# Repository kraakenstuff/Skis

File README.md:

# Skis

This is smd version of Bastl Skis v1. Main differences are:

* It has skis (two sliders) vs. no skis in Bastl version
* 6HP vs. 5HP, for obvious, OCD reasons
* Range switch vs. range backside jumper (although this switch works as a jumper - instead of going from freq0 to freq1, and then from freq1 to freq2 in the second position, it goes from freq0 to freq1, and then from freq0 to freq2)
* Version 2 of Bastl Skis has decay CV input, and this one doesn't have it
* Version 1 of Bastl Skis was THT and had two sandwiched boards, and this one is SMT in one board.

Status: tested and working.

CC-BY-SA
Václav Peloušek
bastl-instruments.com

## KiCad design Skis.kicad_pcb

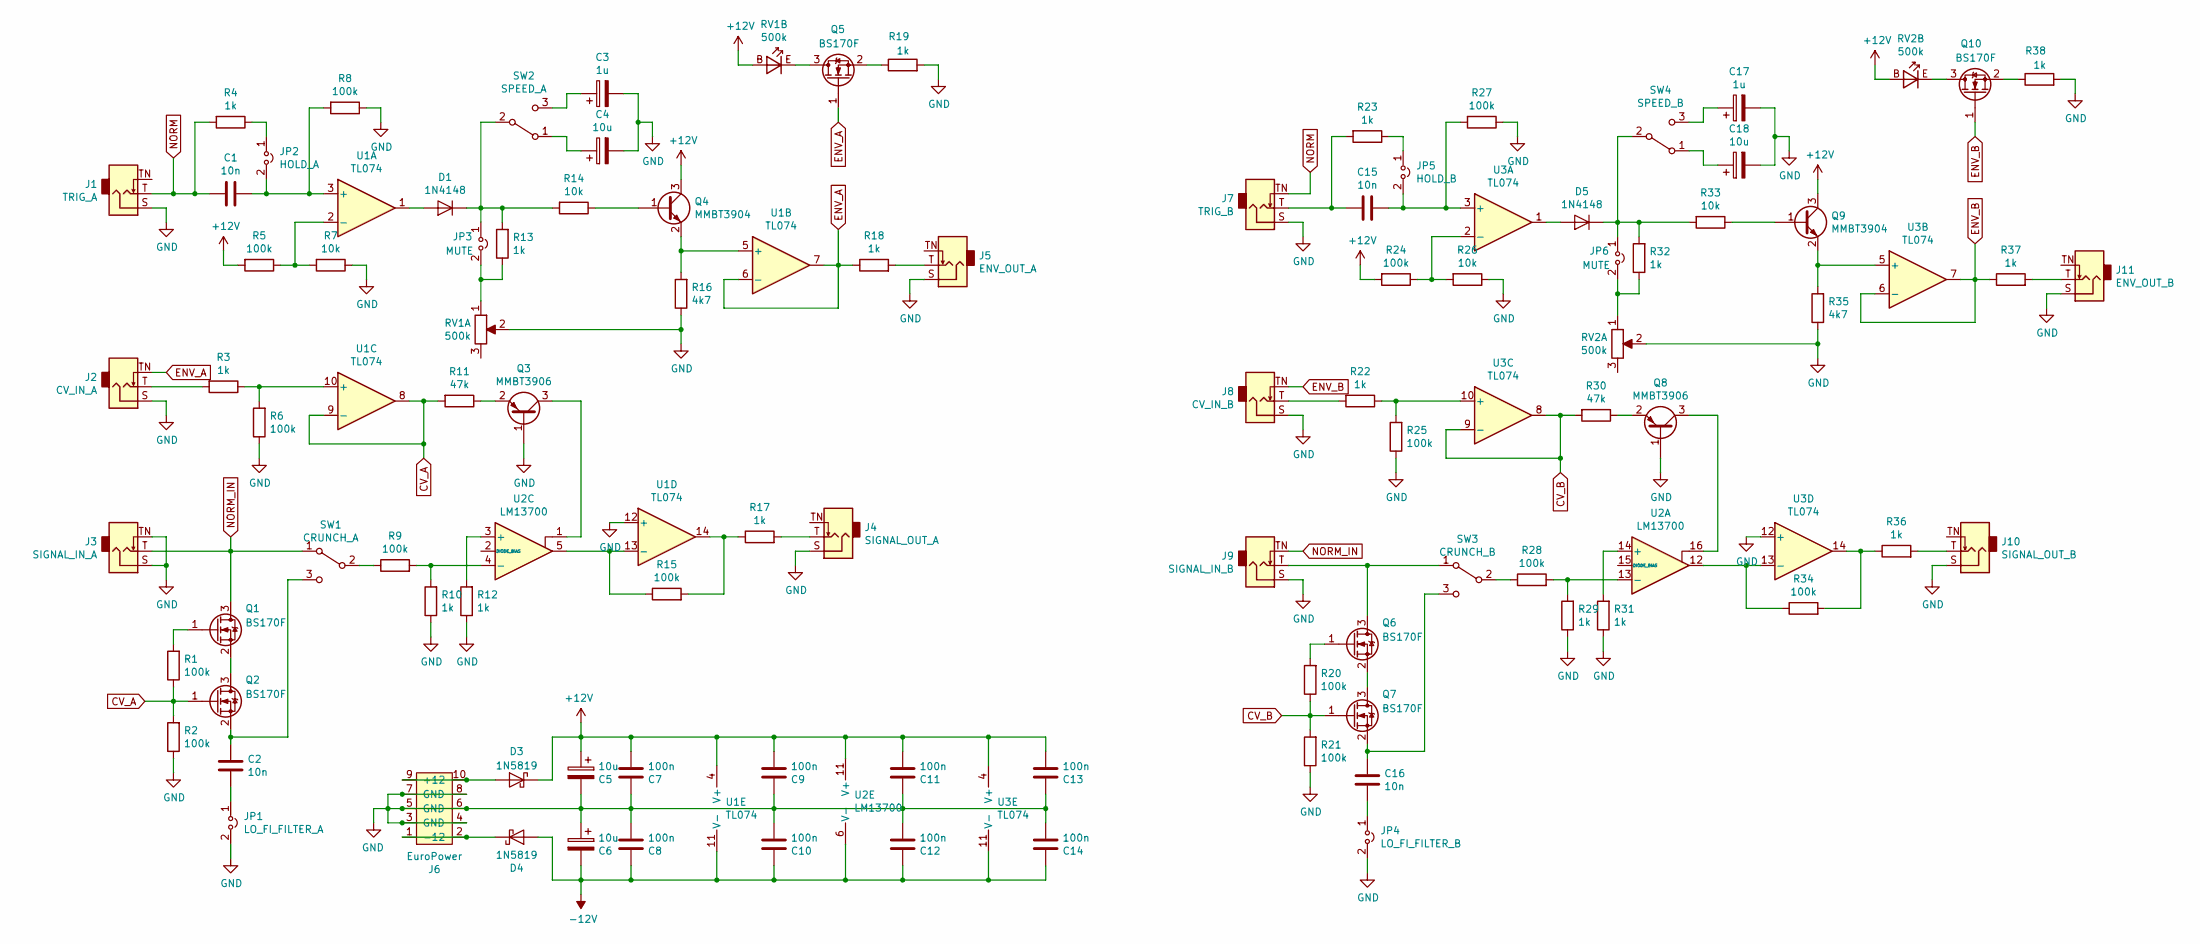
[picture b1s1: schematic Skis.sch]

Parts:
C1, C2, C15, C16: 10n; C_0603_1608Metric_Pad1.05x0.95mm_HandSolder
C3, C17: 1u; CP_Elec_4x5.8
C4, C5, C6, C18: 10u; CP_Elec_5x5.8
C7, C8, C9, C10, C11, C12, C13, C14: 100n; C_0603_1608Metric_Pad1.05x0.95mm_HandSolder
D1, D5: 1N4148; D_0603_1608Metric_Pad1.05x0.95mm_HandSolder
D3, D4: 1N5819; D_SOD-123
J1: TRIG_A; PJ301M-12-NoHole
J2: CV_IN_A; PJ301M-12-NoHole
J3: SIGNAL_IN_A; PJ301M-12-NoHole
J4: SIGNAL_OUT_A; PJ301M-12-NoHole
J5: ENV_OUT_A; PJ301M-12-NoHole
J6: EuroPower; EuroHeader10
J7: TRIG_B; PJ301M-12-NoHole
J8: CV_IN_B; PJ301M-12-NoHole
J9: SIGNAL_IN_B; PJ301M-12-NoHole
J10: SIGNAL_OUT_B; PJ301M-12-NoHole
J11: ENV_OUT_B; PJ301M-12-NoHole
JP1: LO_FI_FILTER_A; Header 1x2
JP2: HOLD_A; Header 1x2
JP3, JP6: MUTE; Header 1x2
JP4: LO_FI_FILTER_B; Header 1x2
JP5: HOLD_B; Header 1x2
Q1, Q2, Q5, Q6, Q7, Q10: BS170F; SOT-23
Q3, Q8: MMBT3906; SOT-23
Q4, Q9: MMBT3904; SOT-23
R1, R2, R5, R6, R8, R9, R15, R20, R21, R24, R25, R27, R28, R34: 100k; R_0603_1608Metric_Pad1.05x0.95mm_HandSolder
R3, R4, R10, R12, R13, R17, R18, R19, R22, R23, R29, R31, R32, R36, R37, R38: 1k; R_0603_1608Metric_Pad1.05x0.95mm_HandSolder
R7, R14, R26, R33: 10k; R_0603_1608Metric_Pad1.05x0.95mm_HandSolder
R11, R30: 47k; R_0603_1608Metric_Pad1.05x0.95mm_HandSolder
R16, R35: 4k7; R_0603_1608Metric_Pad1.05x0.95mm_HandSolder
RV1, RV2: 500k; PTL30
SW1: CRUNCH_A; SubSwitch_SPDT
SW2: SPEED_A; SubSwitch_SPDT
SW3: CRUNCH_B; SubSwitch_SPDT
SW4: SPEED_B; SubSwitch_SPDT
U1, U3: TL074; SSOP-14_5.3x6.2mm_P0.65mm
U2: LM13700; SOIC-16W_5.3x10.2mm_P1.27mm

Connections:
+12V: C5.1, C7.1, C9.1, C11.1, C13.1, D3.1 (K), Q4.3 (C), Q9.3 (C), R5.2, R24.2, RV1.B, RV2.B, U1.4 (V+), U2.11 (V+), U3.4 (V+)
-12V: C6.2, C8.2, C10.2, C12.2, C14.2, D4.2 (A), U1.11 (V-), U2.6 (V-), U3.11 (V-)
CV_A: Q2.1 (G), R1.1, R2.2, R11.2, U1.8, U1.9 (-)
CV_B: Q7.1 (G), R20.1, R21.2, R30.2, U3.8, U3.9 (-)
ENV_A: J2.TN, Q5.1 (G), R18.1, U1.6 (-), U1.7
ENV_B: J8.TN, Q10.1 (G), R37.1, U3.6 (-), U3.7
GND: C3.2, C4.2, C5.2, C6.1, C7.2, C8.1, C9.2, C10.1, C11.2, C12.1, C13.2, C14.1, C17.2, C18.2, J1.S, J2.S, J3.S, J3.TN, J4.S, J5.S, J6.3 (GND), J6.4, J6.5 (GND), J6.6, J6.7 (GND), J6.8, J7.S, J8.S, J9.S, J10.S, J11.S, JP1.2, JP4.2, Q3.1 (B), Q8.1 (B), R2.1, R6.1, R7.1, R8.1, R10.1, R12.1, R16.1, R19.2, R21.1, R25.1, R26.1, R27.1, R29.1, R31.1, R35.1, R38.2, RV1.2, RV2.2, U1.12 (+), U3.12 (+)
NORM: C1.2, J1.T, J7.TN, R4.2
NORM_IN: J3.T, J9.TN, Q1.3 (D), SW1.1 (A)
unnamed: C1.1, JP2.2, R8.2, U1.3 (+)
unnamed: C2.1, JP1.1
unnamed: C2.2, Q2.2 (S), SW1.3 (C)
unnamed: C3.1, SW2.3 (C)
unnamed: C4.1, SW2.1 (A)
unnamed: C15.1, JP5.2, R27.2, U3.3 (+)
unnamed: C15.2, J7.T, R23.2
unnamed: C16.1, JP4.1
unnamed: C16.2, Q7.2 (S), SW3.3 (C)
unnamed: C17.1, SW4.3 (C)
unnamed: C18.1, SW4.1 (A)
unnamed: D1.1 (K), JP3.1, R13.2, R14.2, SW2.2 (B)
unnamed: D1.2 (A), U1.1
unnamed: D3.2 (A), J6.9 (+12), J6.10
unnamed: D4.1 (K), J6.1 (-12), J6.2
unnamed: D5.1 (K), JP6.1, R32.2, R33.2, SW4.2 (B)
unnamed: D5.2 (A), U3.1
unnamed: J2.T, R3.2
unnamed: J4.T, R17.2
unnamed: J5.T, R18.2
unnamed: J8.T, R22.2
unnamed: J9.T, Q6.3 (D), SW3.1 (A)
unnamed: J10.T, R36.2
unnamed: J11.T, R37.2
unnamed: JP2.1, R4.1
unnamed: JP3.2, R13.1, RV1.1
unnamed: JP5.1, R23.1
unnamed: JP6.2, R32.1, RV2.1
unnamed: Q1.1 (G), R1.2
unnamed: Q1.2 (S), Q2.3 (D)
unnamed: Q3.2 (E), R11.1
unnamed: Q3.3 (C), U2.1
unnamed: Q4.1 (B), R14.1
unnamed: Q4.2 (E), R16.2, U1.5 (+)
unnamed: Q5.2 (S), R19.1
unnamed: Q5.3 (D), RV1.E
unnamed: Q6.1 (G), R20.2
unnamed: Q6.2 (S), Q7.3 (D)
unnamed: Q8.2 (E), R30.1
unnamed: Q8.3 (C), U2.16
unnamed: Q9.1 (B), R33.1
unnamed: Q9.2 (E), R35.2, U3.5 (+)
unnamed: Q10.2 (S), R38.1
unnamed: Q10.3 (D), RV2.E
unnamed: R3.1, R6.2, U1.10 (+)
unnamed: R5.1, R7.2, U1.2 (-)
unnamed: R9.1, SW1.2 (B)
unnamed: R9.2, R10.2, U2.4 (-)
unnamed: R12.2, U2.3 (+)
unnamed: R15.1, U1.13 (-), U2.5
unnamed: R15.2, R17.1, U1.14
unnamed: R22.1, R25.2, U3.10 (+)
unnamed: R24.1, R26.2, U3.2 (-)
unnamed: R28.1, SW3.2 (B)
unnamed: R28.2, R29.2, U2.13 (-)
unnamed: R31.2, U2.14 (+)
unnamed: R34.1, U2.12, U3.13 (-)
unnamed: R34.2, R36.1, U3.14

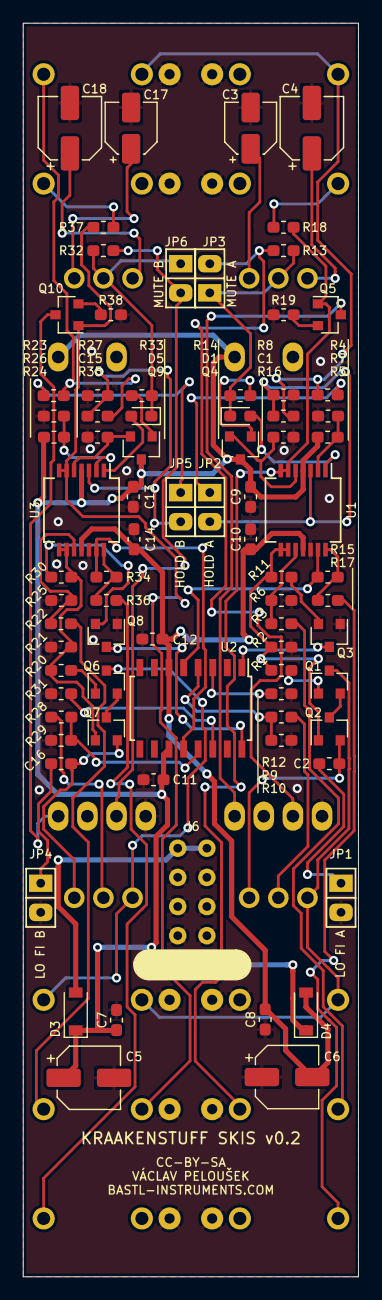
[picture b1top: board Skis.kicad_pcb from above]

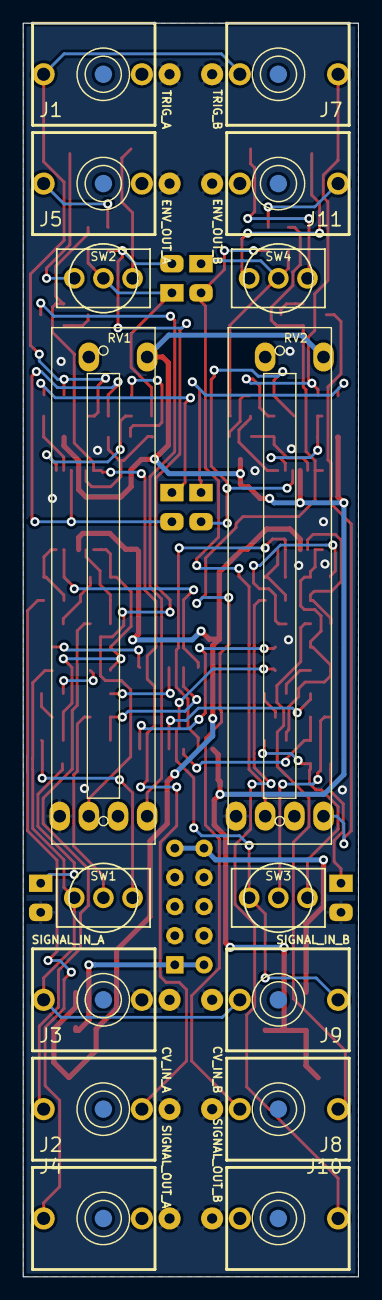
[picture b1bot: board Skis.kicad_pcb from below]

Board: 2 copper layers, 29.2 x 109.2 mm, 96 parts (16 on the bottom side), 67 nets.

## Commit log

2020-04-22 Added panel
2020-04-23 Added normalization for input jacks
2020-04-23 Changed version number on pcb
2020-04-23 Generated gerbers
2021-09-10 Recreated gerber files
